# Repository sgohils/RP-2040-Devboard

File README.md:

https://macondo.hackclub.com/projects/6156

A custom Rp2040 devboard made with everything it need to function, I will use it for my projects and hope to build cool things with it. I followed the tutorial but added many things on my own. Designed in kicad.

# PCB image in kicad

# 3d render

# Schematic

# Bill of materials
| Type | Part Name / Value | Quantity |
| :--- | :--- | :--- |
| Capacitor | 1uF | 2 |
| Capacitor | 0.1uF | 11 |
| Capacitor | 10uF | 2 |
| Capacitor | 33pF | 2 |
| LED | Standard LED | 2 |
| Connector | USB-C Receptacle (USB 2.0 14P) | 1 |
| Header | 20-Pin Header (1x20, 2.54mm) | 2 |
| Header | 3-Pin Header (1x03, 2.54mm) | 1 |
| Resistor | 5.1kΩ | 2 |
| Resistor | 27Ω | 2 |
| Resistor | 1kΩ | 1 |
| Resistor | 10kΩ | 1 |
| Resistor | 1kΩ | 2 |
| Resistor | 470Ω | 1 |
| Resistor | 4.7kΩ | 2 |
| Switch | Push Button (RUN) | 1 |
| Switch | Push Button (BOOTSEL) | 1 |
| Microcontroller | RP2040 | 1 |
| Voltage Regulator | MCP1700x-330xxTT (3.3V LDO) | 1 |
| Flash Memory | W25Q16JVSS (16 Mbit) | 1 |
| Wireless Module | ESP32-WROOM-32 | 1 |
| Crystal Oscillator | 12 MHz | 1 |

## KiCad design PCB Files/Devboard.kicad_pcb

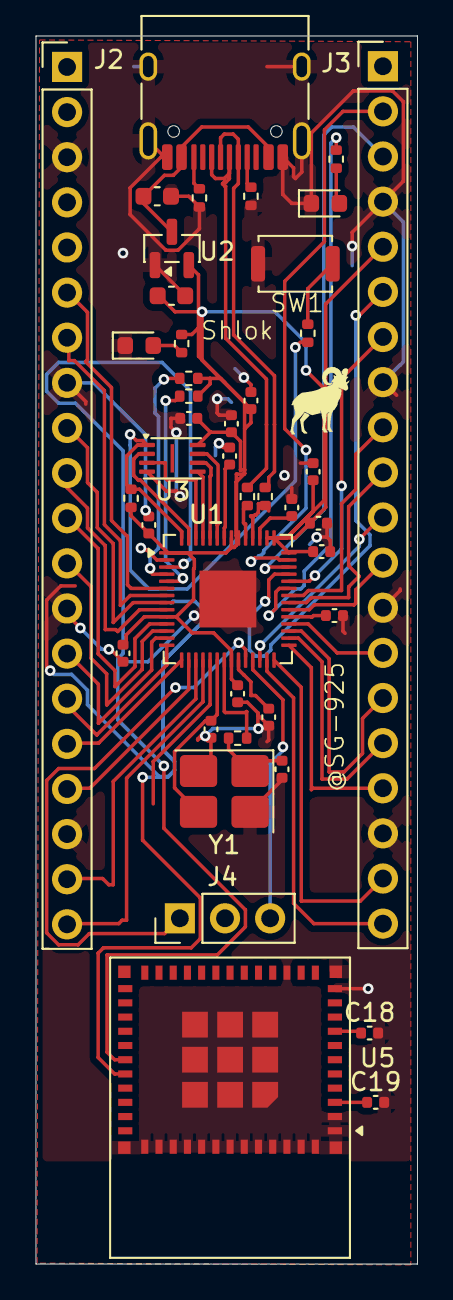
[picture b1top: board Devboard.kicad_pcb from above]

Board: 2 copper layers, 21.5 x 69.1 mm, 42 parts (0 on the bottom side), 56 nets.

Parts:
C1, C10: 1uF; C_0402_1005Metric
C2, C3, C4, C5, C6, C7, C8, C9, C11, C12, C17, C18: 0.1uF; C_0402_1005Metric
C13, C14: 10uF; C_0603_1608Metric
C15, C16: 33pF; C_0402_1005Metric
C19: 10uF; C_0402_1005Metric
D1, D2: LED; LED_0603_1608Metric
J1: USB_C_Receptacle_USB2.0_14P; USB_C_Receptacle_HRO_TYPE-C-31-M-12
J2, J3: Conn_01x20; PinHeader_1x20_P2.54mm_Vertical
J4: Conn_01x03; PinHeader_1x03_P2.54mm_Vertical
R1, R2: 5.1K; R_0402_1005Metric
R3, R4: 27; R_0402_1005Metric
R5: 1K; R_0402_1005Metric
R6: 10k; R_0402_1005Metric
R7, R8: 1k; R_0402_1005Metric
R9: 470; R_0402_1005Metric
R10, R11: 4.7k; R_0402_1005Metric
SW1: SW_Push; SW_Push_SPST_NO_Alps_SKRK
U1: RP2040; QFN-56-1EP_7x7mm_P0.4mm_EP3.2x3.2mm
U2: MCP1700x-330xxTT; SOT-23
U3: W25Q16JVSS; Winbond_USON-8-1EP_3x2mm_P0.5mm_EP0.2x1.6mm
U5: ESP32-C6-MINI-1
Y1: 12 MHz; Crystal_SMD_3225-4Pin_3.2x2.5mm_HandSoldering

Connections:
+1V1: C10.1, C11.1, C12.1, U1.23 (DVDD), U1.45 (VREG_VOUT), U1.50 (DVDD)
+3V3: C1.1, C2.1, C3.1, C4.1, C5.1, C6.1, C7.1, C8.1, C9.1, C14.1, C17.2, C19.1, J3.5, R6.1, R8.2, R10.2, R11.1, U1.1 (IOVDD), U1.10 (IOVDD), U1.22 (IOVDD), U1.33 (IOVDD), U1.42 (IOVDD), U1.43 (ADC_AVDD), U1.44 (VREG_VIN), U1.48 (USB_VDD), U1.49 (IOVDD), U2.2 (VO), U3.8 (VCC), U5.3 (3V3)
/USB_N: R3.2, U1.46 (USB_DM)
/USB_P: R4.2, U1.47 (USB_DP)
ESP_RX: U1.2 (GPIO0), U5.31 (TXD0)
ESP_TX: U1.3 (GPIO1), U5.30 (RXD0)
GND: C1.2, C2.2, C3.2, C4.2, C5.2, C6.2, C7.2, C8.2, C9.2, C10.2, C11.2, C12.2, C13.2, C14.2, C15.1, C16.1, C17.1, C18.2, C19.2, D1.1 (K), D2.1 (K), J1.A1 (GND), J1.A12 (GND), J1.B1 (GND), J1.B12 (GND), J1.SH (SHIELD), J2.3, J2.8, J2.13, J2.18, J3.4, J3.8, J3.13, J3.18, J4.2, R1.2, R2.2, SW1.1, U1.19 (TESTEN), U1.57 (GND), U2.1 (GND), U3.4 (GND), U5.1 (GND), U5.2 (GND), U5.11 (GND), U5.14 (GND), U5.36 (GND), U5.37 (GND), U5.38 (GND), U5.39 (GND), U5.40 (GND), U5.41 (GND), U5.42 (GND), U5.43 (GND), U5.44 (GND), U5.45 (GND), U5.46 (GND), U5.47 (GND), U5.48 (GND), U5.49 (GND), U5.50 (GND), U5.51 (GND), U5.52 (GND), U5.53 (GND), Y1.2 (G), Y1.4 (G)
GPIO2: R10.1, U1.4 (GPIO2)
GPIO3: R11.2, U1.5 (GPIO3)
GPIO4: J2.6, U1.6 (GPIO4)
GPIO5: J2.7, U1.7 (GPIO5)
GPIO6: J2.9, U1.8 (GPIO6)
GPIO7: J2.10, U1.9 (GPIO7)
GPIO8: J2.11, U1.11 (GPIO8)
GPIO9: J2.12, U1.12 (GPIO9)
GPIO10: J2.14, U1.13 (GPIO10)
GPIO11: J2.15, U1.14 (GPIO11)
GPIO12: J2.16, U1.15 (GPIO12)
GPIO13: J2.17, U1.16 (GPIO13)
GPIO14: J2.19, U1.17 (GPIO14)
GPIO15: J2.20, U1.18 (GPIO15)
GPIO16: J3.20, U1.27 (GPIO16)
GPIO17: J3.19, U1.28 (GPIO17)
GPIO18: J3.17, U1.29 (GPIO18)
GPIO19: J3.16, U1.30 (GPIO19)
GPIO20: J3.15, U1.31 (GPIO20)
GPIO21: J3.14, U1.32 (GPIO21)
GPIO22: J3.12, U1.34 (GPIO22)
GPIO23: J3.10, U1.35 (GPIO23)
GPIO24: J3.9, U1.36 (GPIO24)
GPIO25: R9.2, U1.37 (GPIO25)
GPIO26_ADC0: J3.7, U1.38 (GPIO26/ADC0)
GPIO27_ADC1: J3.6, U1.39 (GPIO27/ADC1)
GPIO28_ADC2: J3.3, U1.40 (GPIO28/ADC2)
GPIO29_ADC3: J3.2, U1.41 (GPIO29/ADC3)
unnamed: C16.2, R5.2, Y1.1
unnamed: D1.2 (A), R8.1
unnamed: D2.2 (A), R9.1
unnamed: J1.A5 (CC1), R2.1
unnamed: J1.B5 (CC2), R1.1
unnamed: R7.1, SW1.2
unnamed: C13.1, J1.A4 (VBUS), J1.A9 (VBUS), J1.B4 (VBUS), J1.B9 (VBUS), U2.3 (VI)
unnamed: C18.1, U5.8 (EN)
QSPI_SCLK: U1.52 (QSPI_SCLK), U3.6 (CLK)
QSPI_SD0: U1.53 (QSPI_SD0), U3.5 (DI/IO_{0})
QSPI_SD1: U1.55 (QSPI_SD1), U3.2 (DO/IO_{1})
QSPI_SD2: U1.54 (QSPI_SD2), U3.3 (~WP/IO_{2})
QSPI_SD3: U1.51 (QSPI_SD3), U3.7 (~HOLD/~RESET/IO_{3})
QSPI_SS: R6.2, R7.2, U1.56 (~QSPI_SS), U3.1 (~CS)
RUN: J3.11, U1.26 (RUN)
SWCLK: J4.1, U1.24 (SWCLK)
SWD: J4.3, U1.25 (SWDIO)
USB_D+: J1.A6 (D+), J1.B6 (D+), R4.1
USB_D-: J1.A7 (D-), J1.B7 (D-), R3.1
XIN: C15.2, U1.20 (XIN), Y1.3
XOUT: R5.1, U1.21 (XOUT)

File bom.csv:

"Id";"Designator";"Footprint";"Quantity";"Designation";"Supplier and ref"
1;"C1, C10";"C_0402_1005Metric";2;"1uF";""
2;"C2, C3, C4, C5, C6, C7, C8, C9, C11, C12, C17";"C_0402_1005Metric";11;"0.1uF";""
3;"C13, C14";"C_0603_1608Metric";2;"10uF";""
4;"C15, C16";"C_0402_1005Metric";2;"33pF";""
5;"D1, D2";"LED_0603_1608Metric";2;"LED";""
6;"J1";"USB_C_Receptacle_HRO_TYPE-C-31-M-12";1;"USB_C_Receptacle_USB2.0_14P";""
7;"J2, J3";"PinHeader_1x20_P2.54mm_Vertical";2;"Conn_01x20";""
8;"J4";"PinHeader_1x03_P2.54mm_Vertical";1;"Conn_01x03";""
9;"R1, R2";"R_0402_1005Metric";2;"5.1K";""
10;"R3, R4";"R_0402_1005Metric";2;"27";""
11;"R5";"R_0402_1005Metric";1;"1K";""
12;"R6";"R_0402_1005Metric";1;"10k";""
13;"R7, R8";"R_0402_1005Metric";2;"1k";""
14;"R9";"R_0402_1005Metric";1;"470";""
15;"R10, R11";"R_0402_1005Metric";2;"4.7k";""
16;"SW1";"SW_Push_SPST_NO_Alps_SKRK";1;"RUN Button";""
17;"SW2";"SW_Push_SPST_NO_Alps_SKRK";1;"BOOTSEL Button";""
18;"U1";"QFN-56-1EP_7x7mm_P0.4mm_EP3.2x3.2mm";1;"RP2040";""
19;"U2";"SOT-23";1;"MCP1700x-330xxTT";""
20;"U3";"Winbond_USON-8-1EP_3x2mm_P0.5mm_EP0.2x1.6mm";1;"W25Q16JVSS";""
21;"U4";"MODULE_ESP32-WROOM-32";1;"ESP32-WROOM-32";""
22;"Y1";"Crystal_SMD_3225-4Pin_3.2x2.5mm_HandSoldering";1;"12 MHz";""
